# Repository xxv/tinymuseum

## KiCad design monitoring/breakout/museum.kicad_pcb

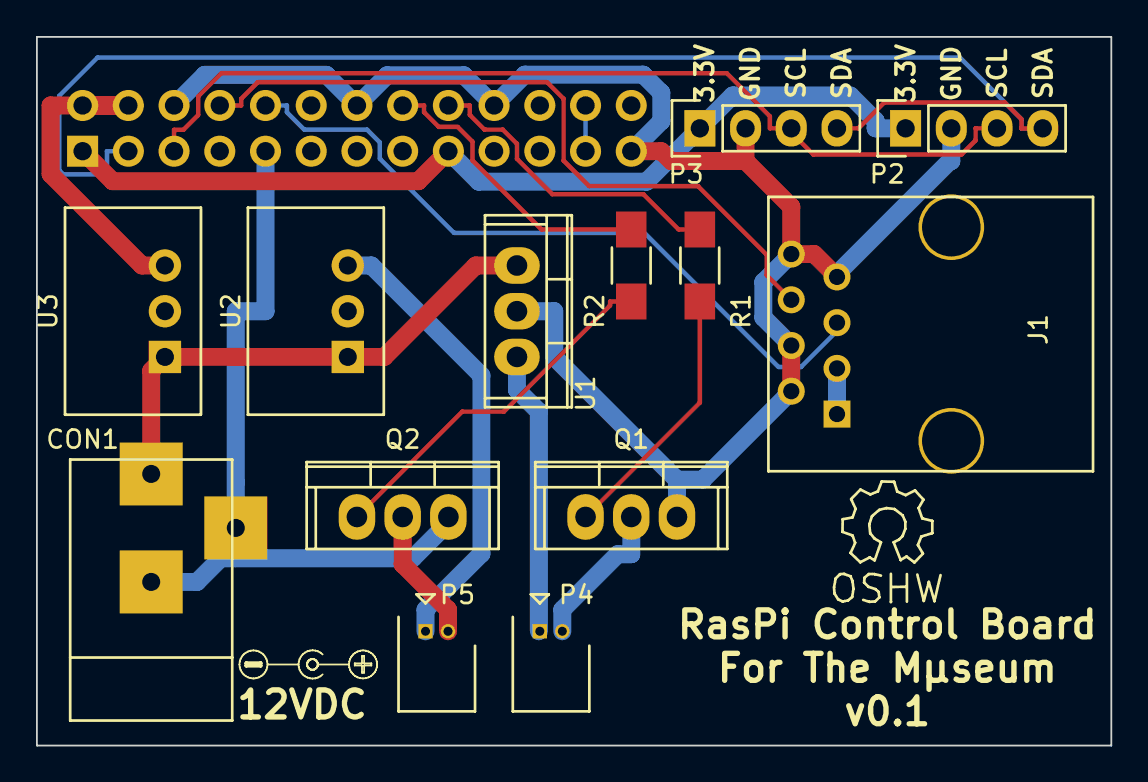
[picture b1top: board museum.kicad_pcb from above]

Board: 2 copper layers, 59.7 x 39.4 mm, 14 parts (1 on the bottom side), 18 nets.

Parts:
CON1: UNREG_VIN; BARREL_JACK
J1: RJ45_TRACER; RJ45_8
P1: CONN_13X2; Socket_Strip_Straight_2x13
P2: I2C_2; Pin_Header_Straight_1x04
P3: I2C_1; Pin_Header_Straight_1x04
P4: 12V_LOAD; Connector_Molex_PicoBlade_53048-0210
P5: 5V_LOAD; Connector_Molex_PicoBlade_53048-0210
Q1, Q2: IRFZ44N; TO-220
R1, R2: 10K; R_1206_HandSoldering
U1: LM7812CT; TO-220
U2, U3: R-785; RECOM_R-78xx

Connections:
12V_BATT: CON1.1, U1.1, U2.1, U3.1
+3.3V: P1.1, P1.17, P2.1, P3.1
+5V: P5.1, U2.3
+12V: P4.1, U1.3
/5V_GND_SW: P5.2, Q2.2
/12V_GND_SW: P4.2, Q1.2
GND: CON1.2, CON1.3, J1.2, J1.4, J1.7, J1.8, P1.6, P1.9, P1.14, P1.20, P1.25, P2.2, P3.2, Q1.3, Q2.3, U1.2, U2.2, U3.2
unnamed: Q1.1, R1.2
unnamed: Q2.1, R2.2
RASPI_5V: P1.2, P1.4, U3.3
RASPI_GPIO_08: P1.23, P1.24
RASPI_GPIO_23: P1.16, R2.1
RASPI_GPIO_24: P1.18, R1.1
RASPI_SCL: P1.5, P2.3, P3.3
RASPI_SDA: P1.3, P2.4, P3.4
RASPI_TXD: J1.6, P1.8
TRACER_12V: J1.1, J1.3
TRACER_TXD: J1.5, P1.10

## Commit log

2013-06-12 Adds LED bar socket
2013-06-12 Adds docs
2013-06-12 Renders both plugs at once; moves to spaces
2013-06-12 Adds holes to hold wire in place
2013-06-15 Adds led spotlight shade
2013-07-04 Sizes spots better
2013-07-04 Adds in-progress column file
2013-07-14 Adds LED spot magnet holder
2013-07-14 Updates column print
2013-07-14 LED spot magnet: Tweaks model to add support for resistor
2013-07-15 LED magnet holder: Adds polarity key, sizes holes better
2013-07-15 Spotlight shade: moves to two small holes; adds notes on can
2013-07-15 Imports Parametric_Doric_Temple_Building_Set
2013-07-15 LED spot: improves magnet holder parametric design
2013-07-21 Updates LEDBERG socket description
2013-07-21 Moves files into their own directories
2013-07-21 Updates docs on LED track lighting; switches key side
    * This switches which side the flat keying is on the LED spot so that it
    * matches the flat spot on LEDs (marking the cathode, negative).
2013-07-31 Adds humidity and temperature monitoring
    This adds some python scripts that speak to a HIH-6130 and log it
    to a file. This also adds a gnuplot to plot the log.
2013-07-31 Adds .gitignore
2013-07-31 Swaps colors of temp/humidity on plot
2013-08-18 Initial first draft of lock cover
2013-08-18 Improves lock cover
2013-08-18 Lock cover: adds flat part to screw mechanism
2013-08-18 Makes lock cover bigger
2013-08-18 Adds notes and donate button svg
2013-09-04 Updates after install
2013-09-08 Adds a web page showing the current climate
2013-10-12 Increases cylinder resolution
2013-10-12 Updates notes
2013-12-22 Adds Tracer solar regulator interface
2014-05-11 Moved tracer
2014-05-20 Makes the lock cover a little bigger
2014-05-20 Moves tracer to separate repo
2014-05-20 Imports tracer as submodule
2014-06-02 Adds a little stand to prop up the top lights
2014-06-09 Adds electronics box
2014-06-09 More details on lighting
2014-08-22 Updates submodule
2015-05-31 Adds RasPi breakout board schematic
2015-08-30 Updates board
2015-10-08 Adds first pass at portable museum design
2015-10-12 Cut/printed with these parameters
2016-05-15 Control board revisions (v0.2)
    * Fix RECOM footprints
    * Replace MOSFETs with ones whose gate threshold will work for the 3.3v
    Raspi GPIOs
    * Add second 12v MOSFET-switched channel to the Raspi GPIO with PWM
    * Output channels: move from tiny connectors to ones that should be
    better suited for higher-power use (also one that has screw terminals)
2016-05-15 Correct text labels
